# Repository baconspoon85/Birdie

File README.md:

# Birdie
Birdie is 36-key wireless keyboard inspired by Adalyn (Alice/QAZ style)

This as a work in progress. Still need firmware and a case. Feel free to contrtribute if you're interested in moving this along.

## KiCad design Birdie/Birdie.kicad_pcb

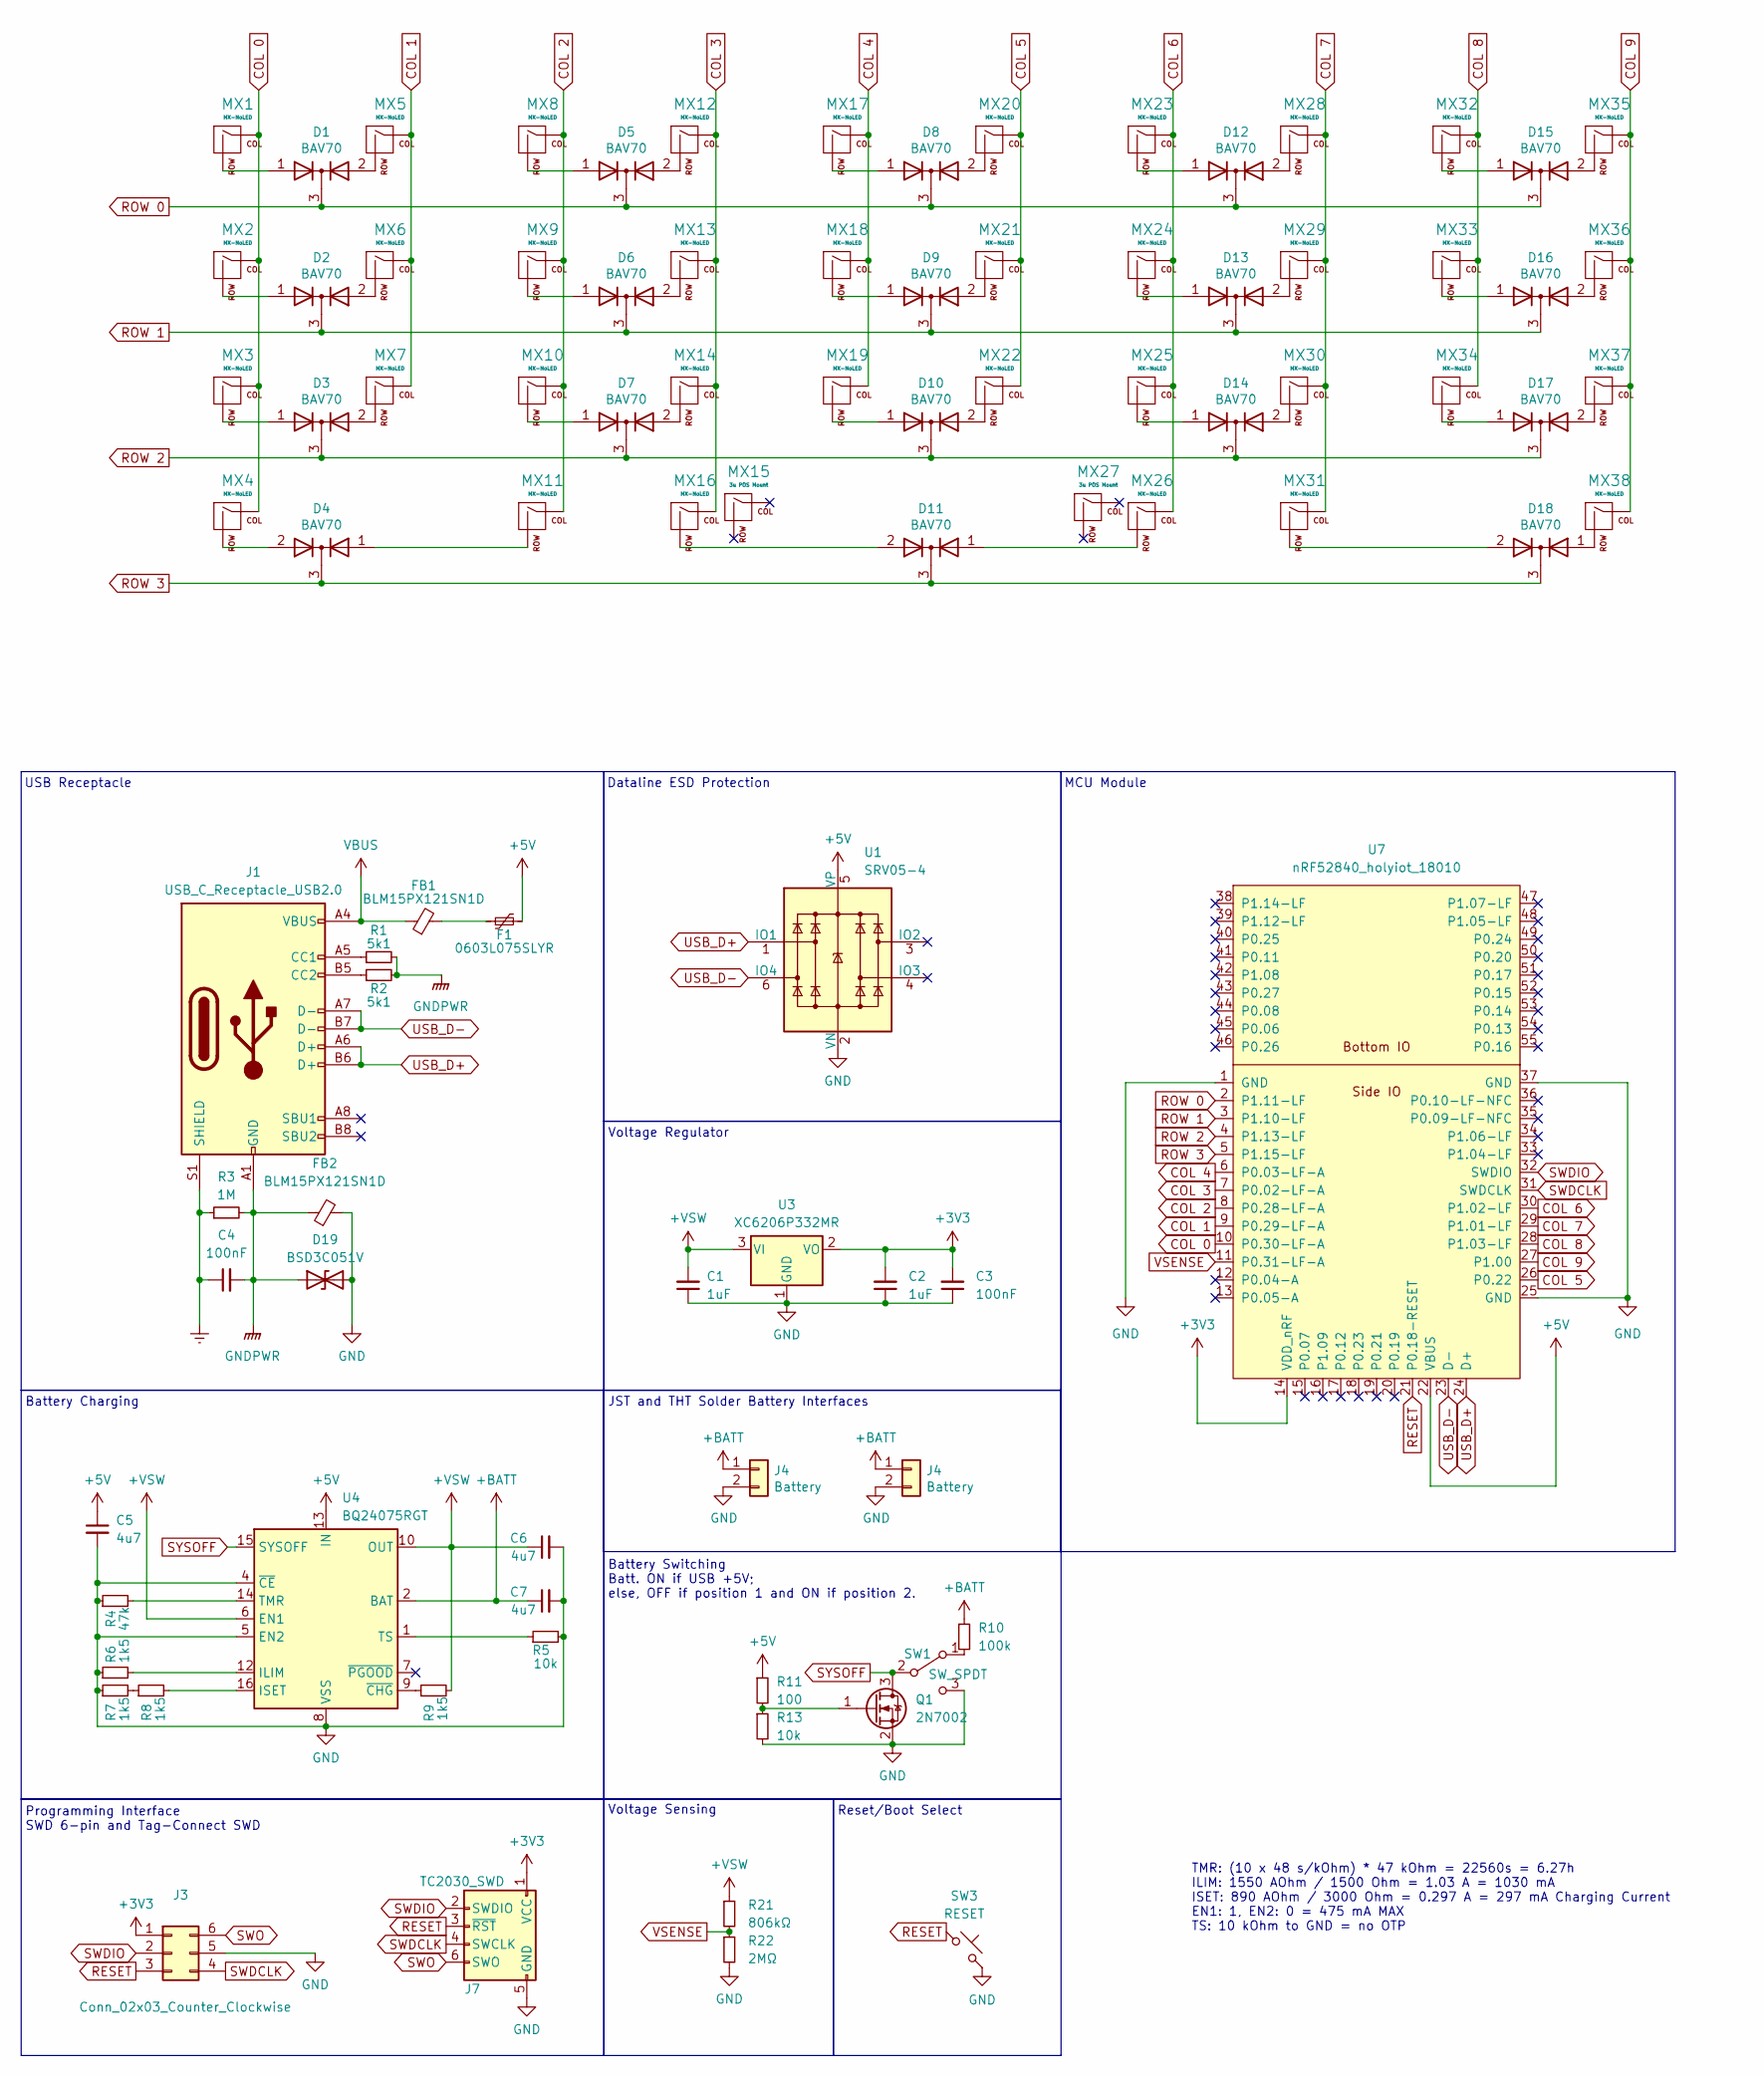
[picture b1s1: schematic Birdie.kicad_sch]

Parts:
C1, C2: 1uF; C_0402_1005Metric; LCSC C52923
C3, C4: 100nF; C_0402_1005Metric; LCSC C2655418
C5, C6, C7: 4u7; C_0402_1005Metric; LCSC C541466
D1: BAV70; SOT-23; LCSC C154830
D2, D3, D4, D5, D6, D7, D8, D9, D10, D11, D12, D13, D14, D15, D16, D17, D18: BAV70; SOT-23
D19: BSD3C051V; D_SOD-323; LCSC C1519956
F1: 0603L075SLYR; Fuse_0603_1608Metric; LCSC C207016
FB1, FB2: BLM15PX121SN1D; L_0402_1005Metric; LCSC C88970
J1: USB_C_Receptacle_USB2.0; USB_C_Receptacle_HRO_TYPE-C-31-M-12; LCSC C165948
J3: Conn_02x03_Counter_Clockwise; PinHeader_2x03_P2.54mm_Vertical
J4: Battery; JST_PH_S2B-PH-K_1x02_P2.00mm_Horizontal
J7: TC2030_SWD; CON_TC2030_outlined
MX1, MX5, MX6, MX7, MX8, MX9, MX10, MX11, MX12, MX13, MX14, MX17, MX18, MX19, MX20, MX21, MX22, MX23, MX24, MX25, MX28, MX29, MX30, MX31, MX32, MX33, MX34, MX36: MX-NoLED; MXOnly-1U-Hotswap
MX2, MX35, MX38: MX-NoLED; MXOnly-1.25U-Hotswap
MX3: MX-NoLED; MXOnly-1.75U-Hotswap
MX4, MX37: MX-NoLED; MXOnly-1.5U-Hotswap
MX15, MX27: 3u POS Mount; MXOnly-1U-Hotswap
MX16, MX26: MX-NoLED; MXOnly-2U-Hotswap-ReversedStabilizers
Q1: 2N7002; SOT-23; LCSC C8545
R1, R2: 5k1; R_0402_1005Metric; LCSC C103086
R3: 1M; R_0603_1608Metric; LCSC C3016422
R4: 47k; R_0402_1005Metric; LCSC C5455484
R5, R13: 10k; R_0402_1005Metric; LCSC C705657
R6, R7, R8, R9: 1k5; R_0402_1005Metric; LCSC C3015796
R10: 100k; R_0402_1005Metric; LCSC C319963
R11: 100; R_0402_1005Metric; LCSC C319948
R21: 806kΩ; R_0402_1005Metric; LCSC C3016043
R22: 2MΩ; R_0402_1005Metric; LCSC C3015935
SW1: SW_SPDT; SW_SPDT_PCM12; LCSC C221841
SW3: RESET; SW_SPST_TL3342; LCSC C318884
U1: SRV05-4; SOT-23-6-routable; LCSC C2972082
U3: XC6206P332MR; SOT-23-3; LCSC C5250985
U4: BQ24075RGT; VQFN-16-1EP_3x3mm_P0.5mm_EP1.6x1.6mm; LCSC C2865459
U7: nRF52840_holyiot_18010

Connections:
+3V3: C2.2, C3.2, J3.1, U3.2 (VO); also elsewhere on the board
+5V: C5.1, F1.2, R11.1, U1.5 (VP), U4.13 (IN); also elsewhere on the board
+BATT: C7.1, J4.1, R10.1, U4.2 (BAT), U4.3 (BAT); also elsewhere on the board
+VSW: C1.2, C6.1, R9.2, U3.3 (VI), U4.6 (EN1), U4.10 (OUT), U4.11 (OUT); also elsewhere on the board
COL 0: MX1.1 (COL), MX2.1 (COL), MX3.1 (COL), MX4.1 (COL); also elsewhere on the board
COL 1: MX5.1 (COL), MX6.1 (COL), MX7.1 (COL); also elsewhere on the board
COL 2: MX8.1 (COL), MX9.1 (COL), MX10.1 (COL), MX11.1 (COL); also elsewhere on the board
COL 3: MX12.1 (COL), MX13.1 (COL), MX14.1 (COL), MX16.1 (COL); also elsewhere on the board
COL 4: MX17.1 (COL), MX18.1 (COL), MX19.1 (COL); also elsewhere on the board
COL 5: MX20.1 (COL), MX21.1 (COL), MX22.1 (COL); also elsewhere on the board
COL 6: MX23.1 (COL), MX24.1 (COL), MX25.1 (COL), MX26.1 (COL); also elsewhere on the board
COL 7: MX28.1 (COL), MX29.1 (COL), MX30.1 (COL), MX31.1 (COL); also elsewhere on the board
COL 8: MX32.1 (COL), MX33.1 (COL), MX34.1 (COL); also elsewhere on the board
COL 9: MX35.1 (COL), MX36.1 (COL), MX37.1 (COL), MX38.1 (COL); also elsewhere on the board
Earth: C4.1, J1.S1 (SHIELD), R3.1
GND: C1.1, C2.1, C3.1, C5.2, C6.2, C7.2, D19.2 (A2), FB2.2, J3.5, J4.2, Q1.2 (S), R4.1, R5.2, R6.1, R7.1, R13.2, SW1.3 (C), U1.2 (VN), U3.1 (GND), U4.4 (~CE), U4.5 (EN2), U4.8 (VSS), U4.17 (VSS); also elsewhere on the board
GNDPWR: C4.2, D19.1 (A1), FB2.1, J1.A1 (GND), J1.A12 (GND), J1.B1 (GND), J1.B12 (GND), R1.2, R2.2, R3.2
unnamed: F1.1, FB1.2
unnamed: J1.A5 (CC1), R1.1
unnamed: J1.B5 (CC2), R2.1
unnamed: D1.1 (A), MX1.2 (ROW)
unnamed: D2.1 (A), MX2.2 (ROW)
unnamed: D3.1 (A), MX3.2 (ROW)
unnamed: D4.2 (A), MX4.2 (ROW)
unnamed: D1.2 (A), MX5.2 (ROW)
unnamed: D2.2 (A), MX6.2 (ROW)
unnamed: D3.2 (A), MX7.2 (ROW)
unnamed: D5.1 (A), MX8.2 (ROW)
unnamed: D6.1 (A), MX9.2 (ROW)
unnamed: D7.1 (A), MX10.2 (ROW)
unnamed: D4.1 (A), MX11.2 (ROW)
unnamed: D5.2 (A), MX12.2 (ROW)
unnamed: D6.2 (A), MX13.2 (ROW)
unnamed: D7.2 (A), MX14.2 (ROW)
unnamed: D11.2 (A), MX16.2 (ROW)
unnamed: D8.1 (A), MX17.2 (ROW)
unnamed: D9.1 (A), MX18.2 (ROW)
unnamed: D10.1 (A), MX19.2 (ROW)
unnamed: D8.2 (A), MX20.2 (ROW)
unnamed: D9.2 (A), MX21.2 (ROW)
unnamed: D10.2 (A), MX22.2 (ROW)
unnamed: D12.1 (A), MX23.2 (ROW)
unnamed: D13.1 (A), MX24.2 (ROW)
unnamed: D14.1 (A), MX25.2 (ROW)
unnamed: D11.1 (A), MX26.2 (ROW)
unnamed: D12.2 (A), MX28.2 (ROW)
unnamed: D13.2 (A), MX29.2 (ROW)
unnamed: D14.2 (A), MX30.2 (ROW)
unnamed: D18.2 (A), MX31.2 (ROW)
unnamed: D15.1 (A), MX32.2 (ROW)
unnamed: D16.1 (A), MX33.2 (ROW)
unnamed: D17.1 (A), MX34.2 (ROW)
unnamed: D15.2 (A), MX35.2 (ROW)
unnamed: D16.2 (A), MX36.2 (ROW)
unnamed: D17.2 (A), MX37.2 (ROW)
unnamed: D18.1 (A), MX38.2 (ROW)
unnamed: Q1.1 (G), R11.2, R13.1
unnamed: R7.2, R8.1
unnamed: R10.2, SW1.1 (A)
unnamed: R6.2, U4.12 (ILIM)
unnamed: R8.2, U4.16 (ISET)
unnamed: R4.2, U4.14 (TMR)
unnamed: R5.1, U4.1 (TS)
unnamed: R9.1, U4.9 (~CHG)
RESET: J3.3; also elsewhere on the board
ROW 0: D1.3 (K), D5.3 (K), D8.3 (K), D12.3 (K), D15.3 (K); also elsewhere on the board
ROW 1: D2.3 (K), D6.3 (K), D9.3 (K), D13.3 (K), D16.3 (K); also elsewhere on the board
ROW 2: D3.3 (K), D7.3 (K), D10.3 (K), D14.3 (K), D17.3 (K); also elsewhere on the board
ROW 3: D4.3 (K), D11.3 (K), D18.3 (K); also elsewhere on the board
SWDCLK: J3.4; also elsewhere on the board
SWDIO: J3.2; also elsewhere on the board
SWO: J3.6; also elsewhere on the board
SYSOFF: Q1.3 (D), SW1.2 (B), U4.15 (SYSOFF)
USB_D+: J1.A6 (D+), J1.B6 (D+), U1.1 (IO1); also elsewhere on the board
USB_D-: J1.A7 (D-), J1.B7 (D-), U1.6 (IO4); also elsewhere on the board
VBUS: FB1.1, J1.A4 (VBUS), J1.A9 (VBUS), J1.B4 (VBUS), J1.B9 (VBUS)

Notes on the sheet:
MCU Module
Reset/Boot Select
Programming Interface SWD 6-pin and Tag-Connect SWD
JST and THT Solder Battery Interfaces
Dataline ESD Protection
TMR: (10 x 48 s/kOhm) * 47 kOhm = 22560s = 6.27h ILIM: 1550 AOhm / 1500 Ohm = 1.03 A = 1030 mA ISET: 890 AOhm / 3000 Ohm = 0.297 A = 297 mA Charging Current EN1: 1, EN2: 0 = 475 mA MAX TS: 10 kOhm to GND = no OTP
USB Receptacle
Voltage Sensing
Battery Charging
Battery Switching Batt. ON if USB +5V; else, OFF if position 1 and ON if position 2.
Voltage Regulator

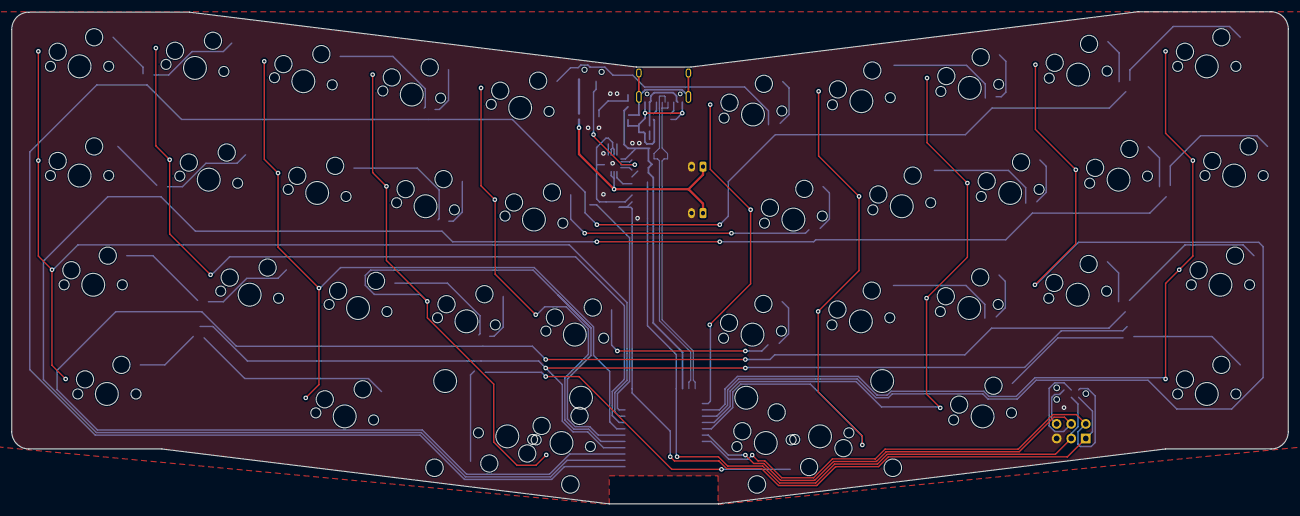
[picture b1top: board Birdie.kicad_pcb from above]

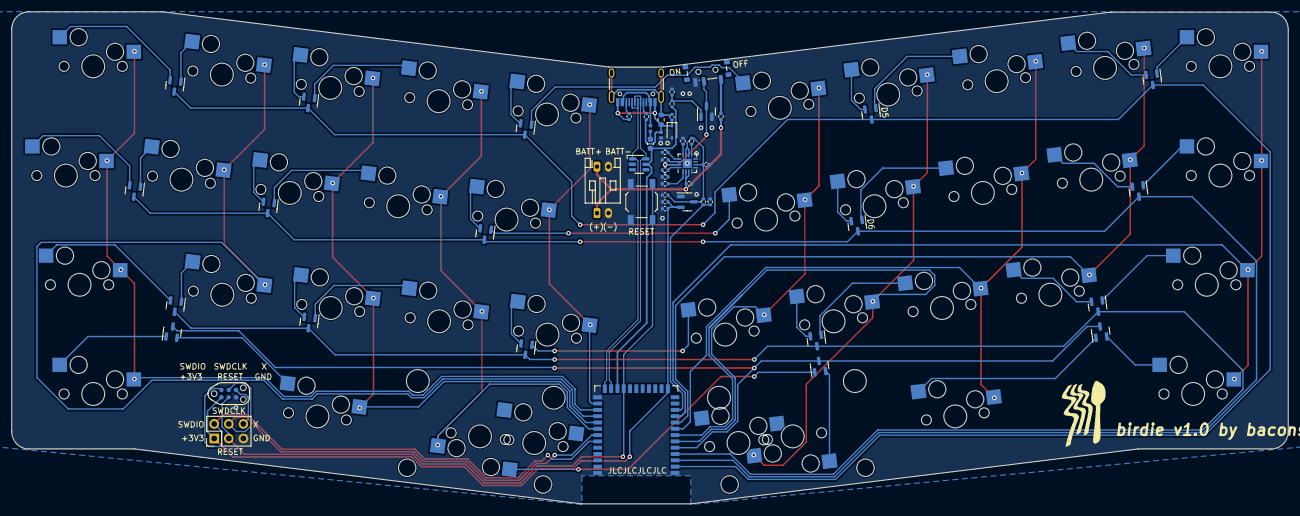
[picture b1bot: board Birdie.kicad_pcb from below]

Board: 2 copper layers, 222.7 x 85.8 mm, 94 parts (56 on the bottom side), 77 nets.

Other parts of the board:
G1: LOGO; baconspoon-logo-13x14mm
J2: TC2030_SWD; CON_TC2030_outlined
J5: Battery; JST_PH_S2B-PH-K_1x02_P2.00mm_Horizontal
R12: 806kΩ; R_0402_1005Metric
R14: 2MΩ; R_0402_1005Metric
SW2: RESET; SW_SPST_TL3342
U2: nRF52840_holyiot_18010

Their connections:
+3V3: J2.1 (VCC), U2.14 (VDD_nRF); also elsewhere on the board
+5V: U2.22 (VBUS); also elsewhere on the board
+BATT: J5.1; also elsewhere on the board
+VSW: R12.1; also elsewhere on the board
COL 0: U2.10 (P0.30-LF-A); also elsewhere on the board
COL 1: U2.9 (P0.29-LF-A); also elsewhere on the board
COL 2: U2.8 (P0.28-LF-A); also elsewhere on the board
COL 3: U2.7 (P0.02-LF-A); also elsewhere on the board
COL 4: U2.6 (P0.03-LF-A); also elsewhere on the board
COL 5: U2.26 (P0.22); also elsewhere on the board
COL 6: U2.30 (P1.02-LF); also elsewhere on the board
COL 7: U2.29 (P1.01-LF); also elsewhere on the board
COL 8: U2.28 (P1.03-LF); also elsewhere on the board
COL 9: U2.27 (P1.00); also elsewhere on the board
GND: J2.5 (GND), J5.2, R14.2, SW2.2, U2.1 (GND), U2.25 (GND), U2.37 (GND); also elsewhere on the board
RESET: J2.3 (~RST), SW2.1, U2.21 (P0.18-RESET); also elsewhere on the board
ROW 0: U2.2 (P1.11-LF); also elsewhere on the board
ROW 1: U2.3 (P1.10-LF); also elsewhere on the board
ROW 2: U2.4 (P1.13-LF); also elsewhere on the board
ROW 3: U2.5 (P1.15-LF); also elsewhere on the board
SWDCLK: J2.4 (SWCLK), U2.31 (SWDCLK); also elsewhere on the board
SWDIO: J2.2 (SWDIO), U2.32 (SWDIO); also elsewhere on the board
SWO: J2.6 (SWO); also elsewhere on the board
USB_D+: U2.24 (D+); also elsewhere on the board
USB_D-: U2.23 (D-); also elsewhere on the board
VSENSE: R12.2, R14.1, U2.11 (P0.31-LF-A)

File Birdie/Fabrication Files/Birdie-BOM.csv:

Comment,Designator,Footprint,JLCPCB Part#(optional)
1uF,C1,C_0402_1005Metric,C52923
1uF,C2,C_0402_1005Metric,C52923
100nF,C3,C_0402_1005Metric,C2655418
100nF,C4,C_0402_1005Metric,C2655418
4.7uF,C5,C_0402_1005Metric,C541466
4.7uF,C6,C_0402_1005Metric,C541466
4.7uF,C7,C_0402_1005Metric,C541466
BAV70,D1,SOT-23,C154830
BAV70,D2,SOT-23,C154830
BAV70,D3,SOT-23,C154830
BAV70,D4,SOT-23,C154830
BAV70,D5,SOT-23,C154830
BAV70,D6,SOT-23,C154830
BAV70,D7,SOT-23,C154830
BAV70,D8,SOT-23,C154830
BAV70,D9,SOT-23,C154830
BAV70,D10,SOT-23,C154830
BAV70,D11,SOT-23,C154830
BAV70,D12,SOT-23,C154830
BAV70,D13,SOT-23,C154830
BAV70,D14,SOT-23,C154830
BAV70,D15,SOT-23,C154830
BAV70,D16,SOT-23,C154830
BAV70,D17,SOT-23,C154830
BAV70,D18,SOT-23,C154830
BSD3C051V,D19,D_SOD-323,C151996
0603L075SLYR,F1,Fuse_0603_1608Metric,C207016
BLM15PX121SN1D,FB1,L_0402_1005Metric,C88970
BLM15PX121SN1D,FB2,L_0402_1005Metric,C88970
USB_C_Receptacle_USB2.0,J1,USB_C_Receptacle_HRO_TYPE-C-31-M-12,C165948
Battery,J4,JST_PH_S2B-PH-K_1x02_P2.00mm_Horizontal,C173752
2N7002,Q1,SOT-23,C8545
5k1,R1,R_0402_1005Metric,C103086
5k1,R2,R_0402_1005Metric,C103086
1M,R3,R_0603_1608Metric,C3016422
47k,R4,R_0402_1005Metric,C3015869
10k,R5,R_0402_1005Metric,C705657
1k5,R6,R_0402_1005Metric,C114759
1k5,R7,R_0402_1005Metric,C114759
1k5,R8,R_0402_1005Metric,C114759
1k5,R9,R_0402_1005Metric,C114759
100k,R10,R_0402_1005Metric,C319963
100,R11,R_0402_1005Metric,C319948
806k,R12,R_0402_1005Metric,C3016043
10k,R13,R_0402_1005Metric,C705657
2M,R14,R_0402_1005Metric,C3015935
SW_SPDT,SW1,SW_SPDT_PCM12,C221841
RESET,SW2,SW_SPST_TL3342,C318884
SRV05-4,U1,SOT-23-6-routable,C2972082
XC6206P332MR,U3,SOT-23-3,C2897477
BQ24075RGR,U4,VQFN-16-1EP_3x3mm_P0.5mm_EP1.6x1.6mm,C15464

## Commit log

2023-11-30 Initial Commit
    Add KiCad fabrication files and Illustrator file for physical layout. This one is WIP. Still need to design a case and write firmware. Feel free to contribute.
